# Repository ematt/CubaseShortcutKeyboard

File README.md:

# CubaseShortcutKeyboard

## Introduction ##

This is a simple device designed to be a shortcut for common action in Cubase. It can:
- control the system volume
- mute/unmute the sound
- play/stop
- start recording
- toggle transport cycle
- mark the current selected track as solo

## How it works ##

Using the v-usb library, it emulates a keyboard and a multimedia device.
The rotary encoder controls the volume and it can mute the sound when the encoder's switch is pressed.
Also it has 6 aditional slots for buttons that can be linked to a specific shortcut used by Cubase.
By default it can play/stop, start recording, Toggle transport cycle and mark the selected track  as solo.

## Directories in this repository ##

*CubaseRemote* - Atmel studio project

*eagle_Cubase USB Remote v1.0* - schematics and eagle file

*hex* - generated hex files

*pictures* - pictures of the electronics board

## Requirements ##

**ATmega8** or any other similar AVR microcontroller. If using a different model, some minor fine-tuning of the firmware might be neded. 

**Other electronic components**. See the circuit schematic.

The required software environment:

Atmel Studio 6

## How to build this project ##

1. Use Atmel studio to edit and build the project.
2. Flash with your favorite programmer
3. Profit

## TODO ##

1. Make an ergonomic case

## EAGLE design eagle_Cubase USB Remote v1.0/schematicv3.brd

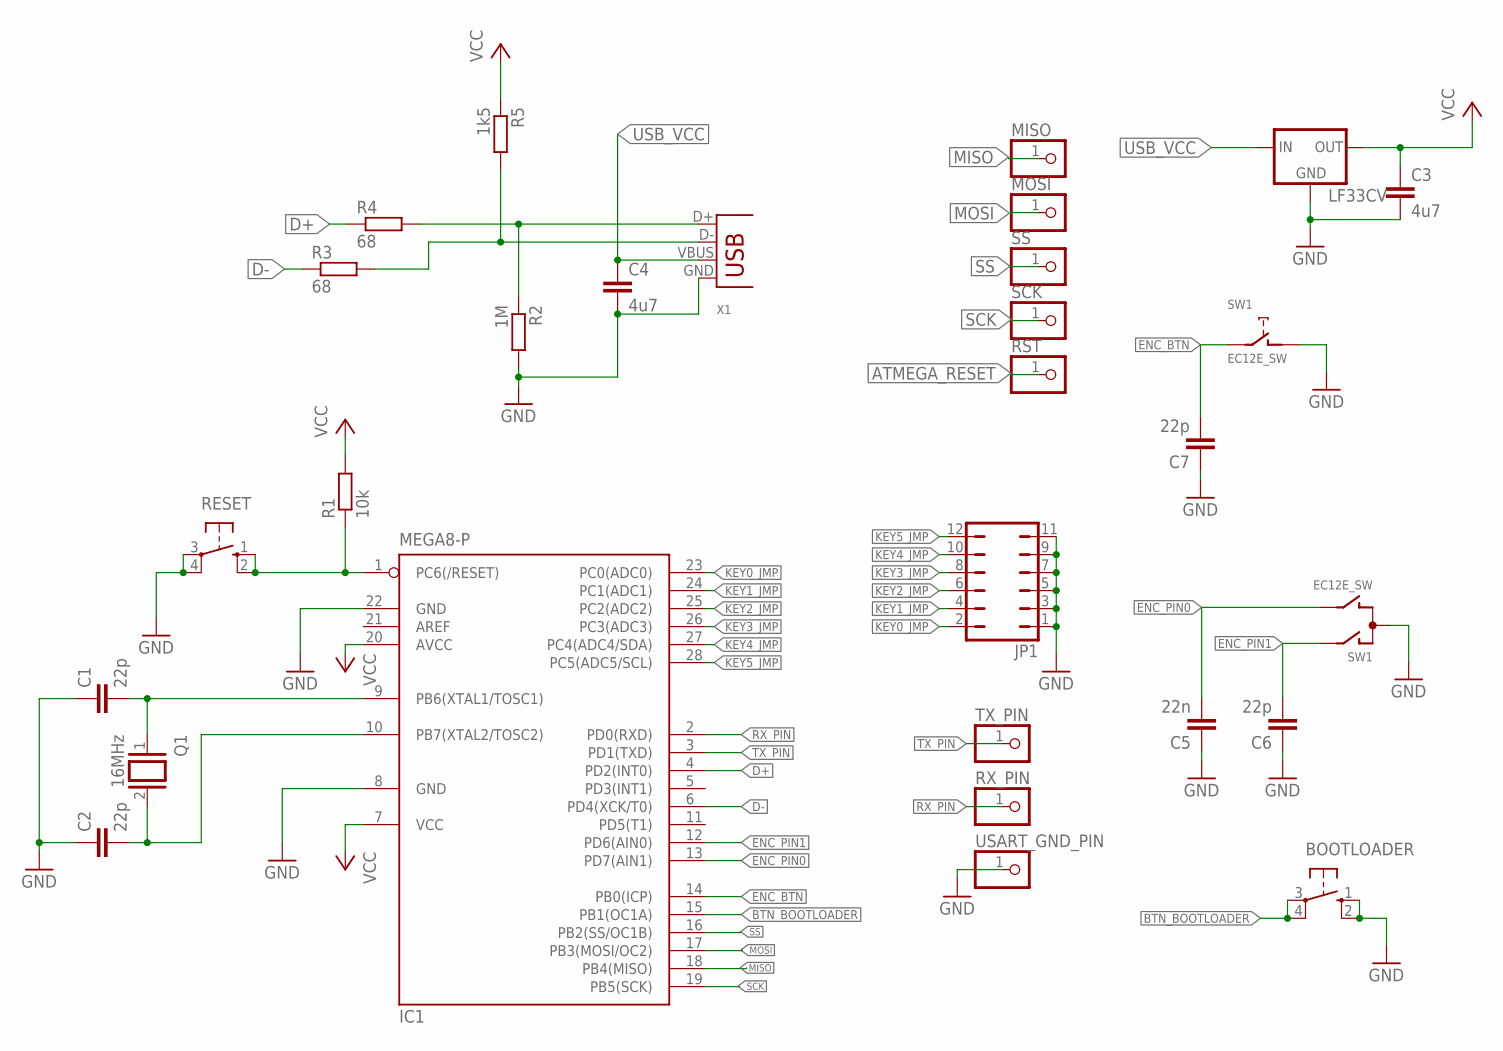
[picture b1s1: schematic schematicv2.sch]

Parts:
BOOTLOADER: 10-XX; B3F-10XX
C1, C2, C6, C7: 22p; C5B5
C3, C4: 4u7; C5B3
C5: 22n; C5B5
IC1: MEGA8-P; DIL28-3
JP1: JP6Q
LF33CV: LFXXCVS; TO220S
MISO: PINHD-1X1; 1X01
MOSI: PINHD-1X1; 1X01
Q1: 16MHz; QS
R1: 10k; 0309V
R2: 1M; 0204/7
R3, R4: 68; 0204/7
R5: 1k5; 0204/7
RESET: 10-XX; B3F-10XX
RST: PINHD-1X1; 1X01
RX_PIN: PINHD-1X1; 1X01
SCK: PINHD-1X1; 1X01
SS: PINHD-1X1; 1X01
SW1: EC12E_SW; ALPS_EC12E_SW
TX_PIN: PINHD-1X1; 1X01
USART_GND_PIN: PINHD-1X1; 1X01
X1: USB-B-H

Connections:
ATMEGA_RESET: IC1.1 (PC6(/RESET)), R1.1, RESET.1 (S), RESET.2 (S1), RST.1
BTN_BOOTLOADER: BOOTLOADER.3, BOOTLOADER.4 (P1), IC1.15 (PB1(OC1A))
D+: IC1.4 (PD2(INT0)), R4.1
D-: IC1.6 (PD4(XCK/T0)), R3.1
ENC_BTN: C7.2, IC1.14 (PB0(ICP)), SW1.E (2)
ENC_PIN0: C5.2, IC1.13 (PD7(AIN1)), SW1.B
ENC_PIN1: C6.2, IC1.12 (PD6(AIN0)), SW1.A
GND: BOOTLOADER.1 (S), BOOTLOADER.2 (S1), C1.1, C2.1, C3.2, C4.2, C5.1, C6.1, C7.1, IC1.8 (GND), IC1.22 (GND), JP1.1, JP1.3, JP1.5, JP1.7, JP1.9, JP1.11, LF33CV.2 (GND), R2.2, RESET.3, RESET.4 (P1), SW1.C, SW1.D (1), USART_GND_PIN.1, X1.GND
KEY0_JMP: IC1.23 (PC0(ADC0)), JP1.2
KEY1_JMP: IC1.24 (PC1(ADC1)), JP1.4
KEY2_JMP: IC1.25 (PC2(ADC2)), JP1.6
KEY3_JMP: IC1.26 (PC3(ADC3)), JP1.8
KEY4_JMP: IC1.27 (PC4(ADC4/SDA)), JP1.10
KEY5_JMP: IC1.28 (PC5(ADC5/SCL)), JP1.12
MISO: IC1.18 (PB4(MISO)), MISO.1
MOSI: IC1.17 (PB3(MOSI/OC2)), MOSI.1
unnamed: C1.2, IC1.9 (PB6(XTAL1/TOSC1)), Q1.1
unnamed: C2.2, IC1.10 (PB7(XTAL2/TOSC2)), Q1.2
unnamed: R2.1, R4.2, X1.D+
unnamed: R3.2, R5.2, X1.D-
RX_PIN: IC1.2 (PD0(RXD)), RX_PIN.1
SCK: IC1.19 (PB5(SCK)), SCK.1
SS: IC1.16 (PB2(SS/OC1B)), SS.1
TX_PIN: IC1.3 (PD1(TXD)), TX_PIN.1
USB_VCC: C4.1, LF33CV.1 (IN), X1.VBUS
VCC: C3.1, IC1.7 (VCC), IC1.20 (AVCC), LF33CV.3 (OUT), R1.2, R5.1

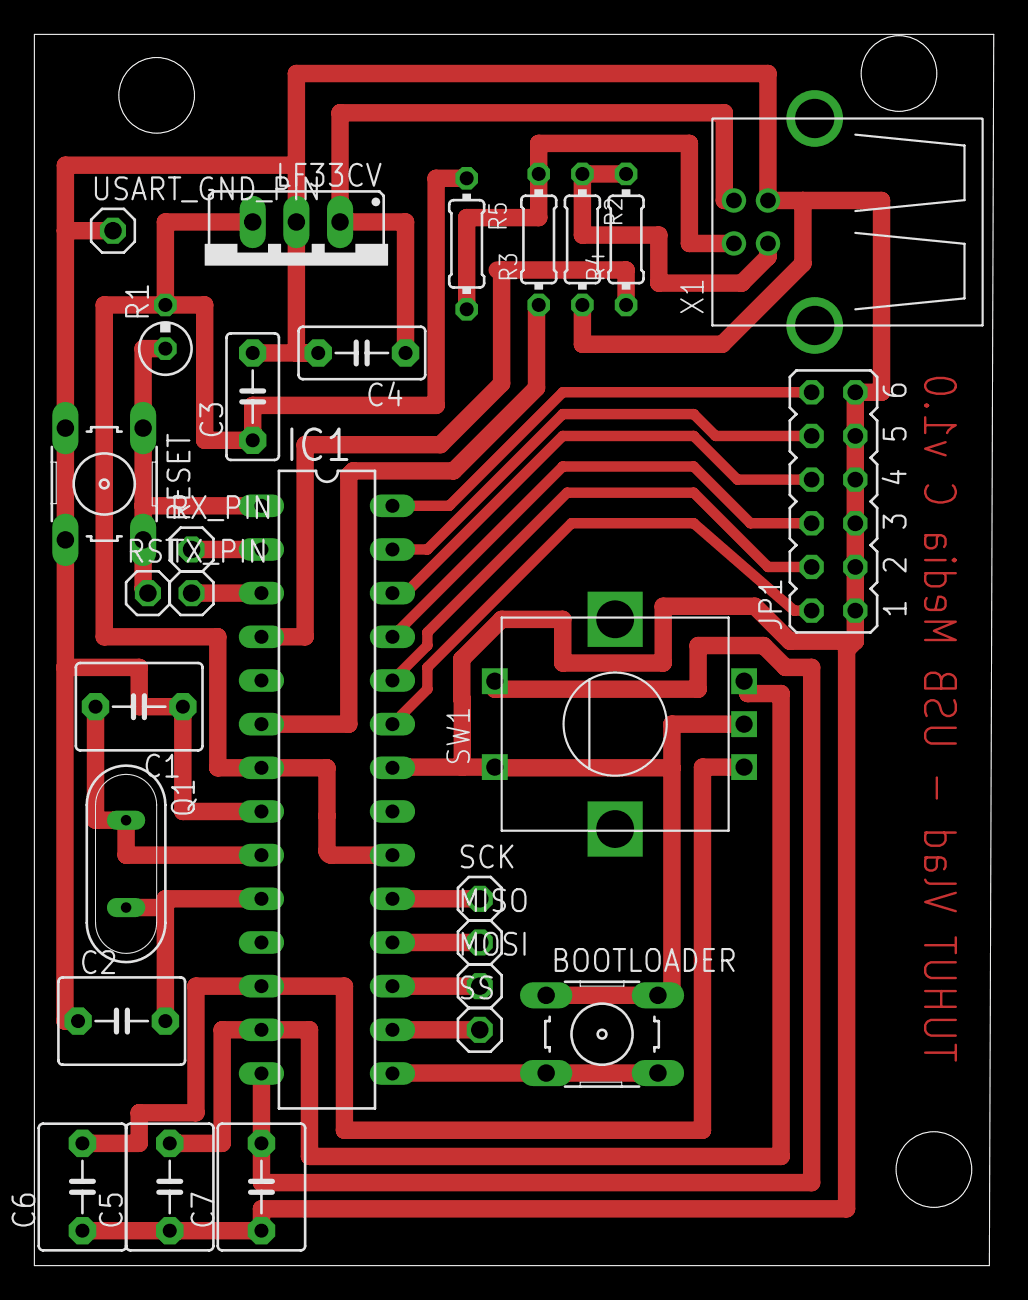
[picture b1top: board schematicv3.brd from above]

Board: 2 copper layers, 55.8 x 71.6 mm, 28 parts (0 on the bottom side), 26 nets.

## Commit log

2018-11-26 Added sources
2018-11-26 added schematic pdf
2019-01-12 Removed Debug files Replaced Encoder code with a modified version of the 'Rotary encoder handler' libray by Ben Buxton
